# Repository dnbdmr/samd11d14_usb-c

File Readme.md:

SAMD11D14 Breakout Board with USB-C
- .5" wide
- Through hole USB-C connector
- QFN-24 Samd11
- All pins except USB broken out

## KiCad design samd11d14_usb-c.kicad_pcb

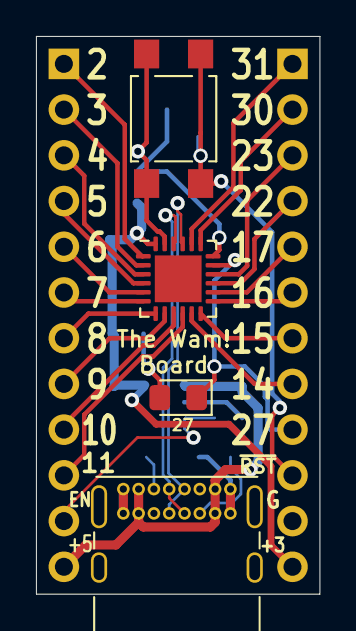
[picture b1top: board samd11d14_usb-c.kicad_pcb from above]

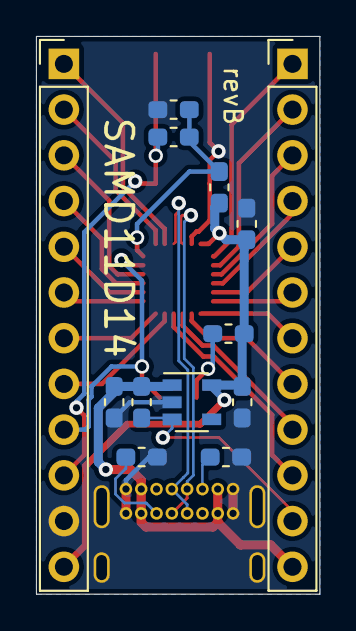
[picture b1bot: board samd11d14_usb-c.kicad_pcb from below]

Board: 2 copper layers, 15.7 x 31.0 mm, 17 parts (13 on the bottom side), 30 nets.

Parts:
C101, C102: 4.7u; C_0603_1608Metric_Pad1.05x0.95mm_HandSolder
C103, C104: 100n; C_0603_1608Metric_Pad1.05x0.95mm_HandSolder
D101: LED_Small; LED_0805_2012Metric_Pad1.15x1.40mm_HandSolder
J101: USB4085-GF-A; USB_C_Receptacle_GCT_USB4085
J102, J103: Conn_01x12_Male; PinHeader_1x12_P2.54mm_Vertical
R101: 100k; R_0603_1608Metric_Pad1.05x0.95mm_HandSolder
R102, R103, R104: 4.7k; R_0603_1608Metric_Pad1.05x0.95mm_HandSolder
R105, R106: 330; R_0603_1608Metric_Pad1.05x0.95mm_HandSolder
SW101: EG5353CT-ND; SW_SPST_TL3305A
U101: AP2127K-3.3; SOT-23-5
U102: ATSAMD11D14A-M; QFN-24-1EP_4x4mm_P0.5mm_EP2.6x2.6mm

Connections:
+3V3: C102.1, C103.1, J103.12, R104.1, R106.2, U101.5, U102.24
+5V: C101.1, J101.A4, J101.A9, J101.B4, J101.B9, J102.12, R101.2, U101.1
/D+: J101.A6, J101.B6, U102.22
/D-: J101.A7, J101.B7, U102.21
/EN: J102.11, R101.1, U101.3
/PA02: J102.1, U102.1
/PA03: J102.2, U102.2
/PA04: J102.3, U102.3
/PA05: J102.4, U102.4
/PA06: J102.5, U102.5
/PA07: J102.6, U102.6
/PA08: J102.7, U102.7
/PA09: J102.8, U102.8
/PA10: J102.9, U102.9
/PA11: J102.10, U102.10
/PA14: J103.8, U102.11
/PA15: J103.7, U102.12
/PA16: J103.6, U102.13
/PA17: J103.5, U102.14
/PA22: J103.4, U102.15
/PA23: J103.3, U102.16
/PA27: D101.1, J103.9, U102.17
/PA30: J103.2, U102.19
/PA31: J103.1, U102.20
/~RESET: J103.10, R105.2, SW101.1
GND: C101.2, C102.2, C103.2, C104.2, J101.A1, J101.A12, J101.B1, J101.B12, J101.S1, J103.11, R102.2, R103.2, SW101.2, U101.2, U102.23
unnamed: C104.1, R104.2, R105.1, U102.18
unnamed: D101.2, R106.1
unnamed: J101.A5, R103.1
unnamed: J101.B5, R102.1

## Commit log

2020-06-11 Added connectors, switch, led
2020-06-11 Finished PCB
2020-06-11 Plotted gerbers and PDF
2020-06-18 Made pcb, updated page details, Rev A.
2020-06-18 Made pcb, updated title blocks, Rev A.
2020-06-18 Wrong value and footprint for C102, fixed.
2020-06-18 Interactive Bom added
2020-06-18 Led D101 backwards, fixed.
2020-06-18 Created pinout spreadsheet
2020-06-18 Create LICENSE
2020-11-13 RevB: width now 0.5", add labels
2020-11-13 Add Readme
2020-11-13 Fix silkscreen
